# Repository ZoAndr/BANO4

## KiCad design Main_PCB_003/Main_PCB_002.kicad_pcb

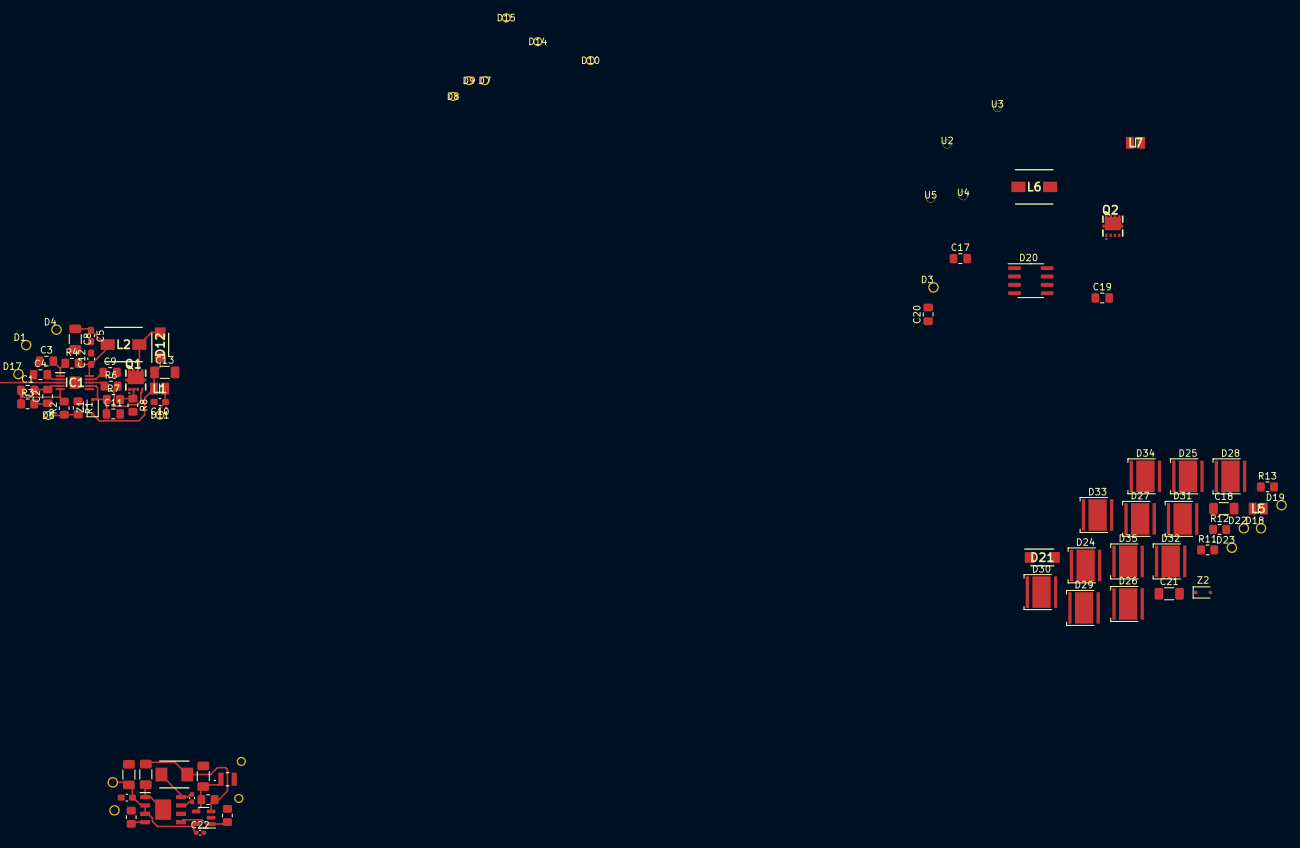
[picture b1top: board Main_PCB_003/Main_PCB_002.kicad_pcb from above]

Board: 4 copper layers, 88 parts (0 on the bottom side), 52 nets.

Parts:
C1, C2, C3, C4, C9, C11, C17, C19, C20: C; C_0805_2012Metric_Pad1.18x1.45mm_HandSolder
C5, C6, C10, C12: C; C_0603_1608Metric_Pad1.08x0.95mm_HandSolder
C7, C8, C13, C15, C16, C18, C21: C; C_1206_3216Metric_Pad1.33x1.80mm_HandSolder
C14, C22: C; C_0402_1005Metric_Pad0.74x0.62mm_HandSolder
D1, D2, D3, D4, D5, D17, D18, D19, D22, D23: WireHole_1p5; WireHole_1p2
D6, D7, D8, D9, D10, D11, D13, D14, D15, D16: Wire_Pad_01; Wire_Hole_1mm
D12, D21: SS36; SODFL4626X120N
D20: TX6211
D24, D25, D26, D27, D28, D29, D30, D31, D32, D33, D34, D35: LED_Cree_XHP50_6V; LED_Cree-XHP50_6V
IC1: TPS40211QDGQRQ1; SOP50P490X110-11N
IC2: LM5164QDDATQ1; SOIC127P600X170-9N
L1, L5, L7: TFM201610ALC-R47MTAA; INDC2016X80N
L2: SRP7050AA-220M; INDPM5752X300N
L3: SRP4020TA-100M; INDPM4441X200N
L4: TFM201610ALC-R47MTAA; WPN252010UR47MT
L6: TFM201610ALC-R47MTAA; INDPM5752X300N
Q1, Q2: AON7407; DFN_3X3_EP
R1, R2, R3, R4, R5, R6, R7, R8, R9, R10, R11, R12, R13: R; R_0805_2012Metric_Pad1.20x1.40mm_HandSolder
U1: INA138; SOT-23-5
U2, U3, U4, U5: Mounting_Hole_M2; Hole_screw_M1p2
Z1, Z2: BZT52-C5V1J; D_SOD-323F

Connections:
GND: C17.2, C18.2, C19.2, C20.2, C21.2, D3.1 (Conn), D19.1 (Conn), D20.1 (GND), R11.2, R13.2, U2.1 (Mnt), U3.1 (Mnt), U4.1 (Mnt), U5.1 (Mnt)
unnamed: C1.1, IC1.5 (FB), R2.2, R3.1
unnamed: C1.2, C2.2, IC1.4 (COMP)
unnamed: C2.1, R3.2
unnamed: C3.2, IC1.1 (RC), R4.1
unnamed: C4.2, IC1.2 (SS)
unnamed: C6.1, C7.1, C22.1, D5.1 (Conn), IC2.2 (VIN), IC2.3 (EN/UVLO), U1.5 (V+)
unnamed: C9.1, IC1.9 (BP)
unnamed: C10.1, D11.1 (Conn), L1.1
unnamed: C3.1, C4.1, C5.2, C8.2, C9.2, C10.2, C11.2, C12.2, C13.2, D1.1 (Conn), IC1.6 (GND), IC1.11 (EP), R1.1, R8.2
unnamed: C11.1, IC1.7 (ISNS), R7.1, Z1.2 (A)
unnamed: C5.1, C8.1, C12.1, D4.1 (Conn), IC1.10 (VDD), L2.1, R4.2
unnamed: C13.1, D12.1, L1.2, Z1.1 (K)
unnamed: C14.1, IC2.8 (SW), L3.1
unnamed: C14.2, IC2.7 (BST)
unnamed: C15.1, L3.2, R9.1, U1.3 (+)
unnamed: C6.2, C7.2, C15.2, C16.2, C22.2, D2.1 (Conn), D16.1 (Conn), IC2.1 (GND), IC2.9 (EP), R5.2, R10.1, U1.2 (GND)
unnamed: C16.1, L4.1, R9.2, U1.4 (-)
unnamed: C17.1, D20.3 (Comp)
unnamed: C18.1, C20.1, D20.2 (En), D20.8 (Vdd), L5.2, L6.1
unnamed: C19.1, D20.7 (TOFF)
unnamed: C21.1, D21.1, L7.1, Z2.1 (K)
unnamed: D6.1 (Conn), R1.2, R2.1
unnamed: D7.1 (Conn), D8.1 (Conn)
unnamed: D9.1 (Conn), D10.1 (Conn)
unnamed: D12.2, L2.2, Q1.5 (D_1), Q1.6 (D_2), Q1.7 (D_3), Q1.8 (D_4), Q1.9, Q1.10, Q1.11
unnamed: D13.1 (Conn), L4.2
unnamed: D14.1 (Conn), D15.1 (Conn)
unnamed: D17.1 (Conn), IC1.3 (DIS/~EN)
unnamed: D18.1 (Conn), L5.1
unnamed: D20.4 (VFB), R12.1, Z2.2 (A)
unnamed: D20.5 (DRV), Q2.4 (G)
unnamed: D20.6 (ICS), Q2.1 (S_1), Q2.2 (S_2), Q2.3 (S_3), R11.1
unnamed: D21.2, L6.2, Q2.5 (D_1), Q2.6 (D_2), Q2.7 (D_3), Q2.8 (D_4)
unnamed: D22.1 (Conn), D35.1 (K), R12.2, R13.1
unnamed: D23.1 (Conn), D24.2 (A), L7.2
unnamed: D24.1 (K), D25.2 (A)
unnamed: D25.1 (K), D26.2 (A)
unnamed: D26.1 (K), D27.2 (A)
unnamed: D27.1 (K), D28.2 (A)
unnamed: D28.1 (K), D29.2 (A)
unnamed: D29.1 (K), D30.2 (A)
unnamed: D30.1 (K), D31.2 (A)
unnamed: D31.1 (K), D32.2 (A)
unnamed: D32.1 (K), D33.2 (A)
unnamed: D33.1 (K), D34.2 (A)
unnamed: D34.1 (K), D35.2 (A)
unnamed: IC1.8 (GDRV), R6.1
unnamed: IC2.4 (RON), R5.1
unnamed: IC2.5 (FB), R10.2, U1.1
unnamed: Q1.1 (S_1), Q1.2 (S_2), Q1.3 (S_3), R7.2, R8.1
unnamed: Q1.4 (G), R6.2

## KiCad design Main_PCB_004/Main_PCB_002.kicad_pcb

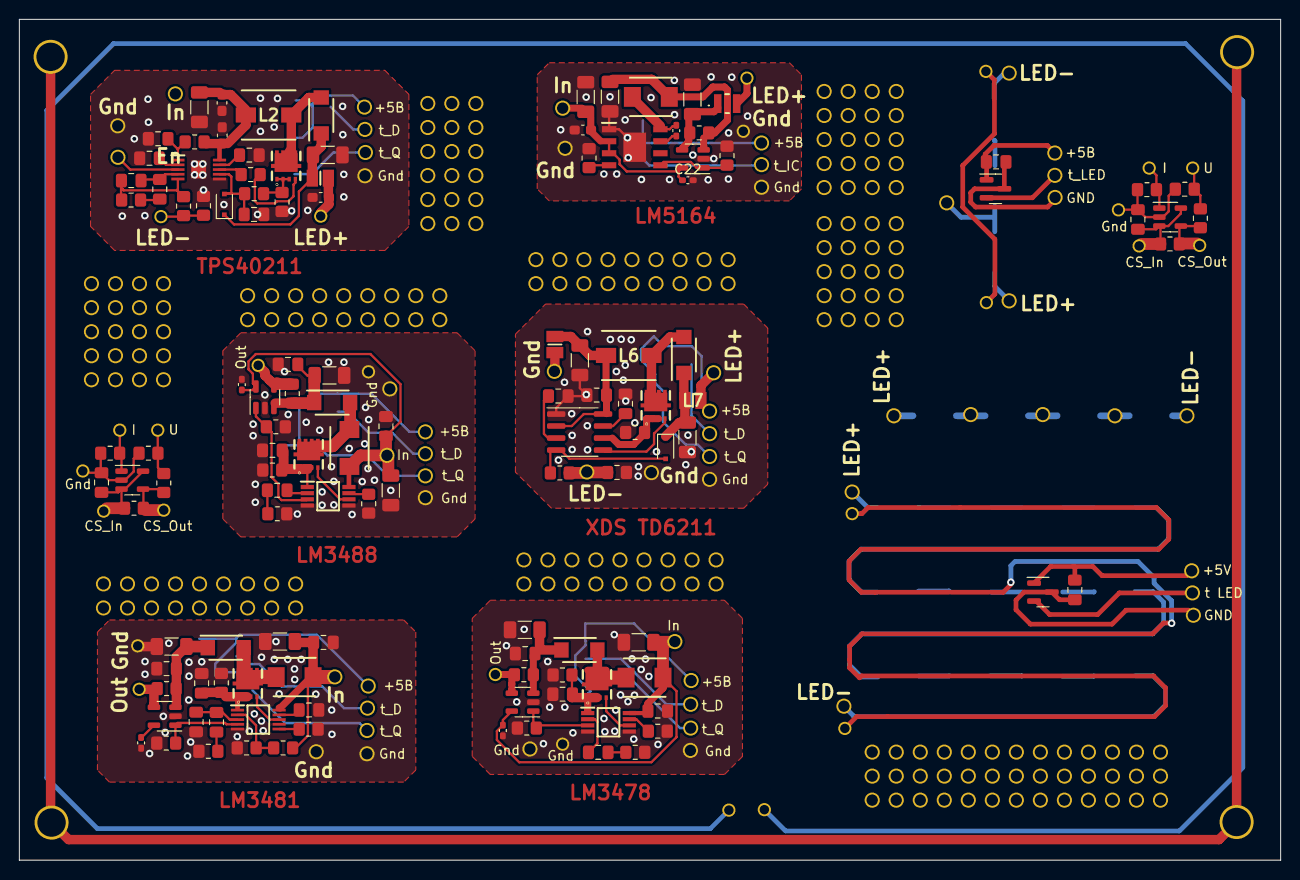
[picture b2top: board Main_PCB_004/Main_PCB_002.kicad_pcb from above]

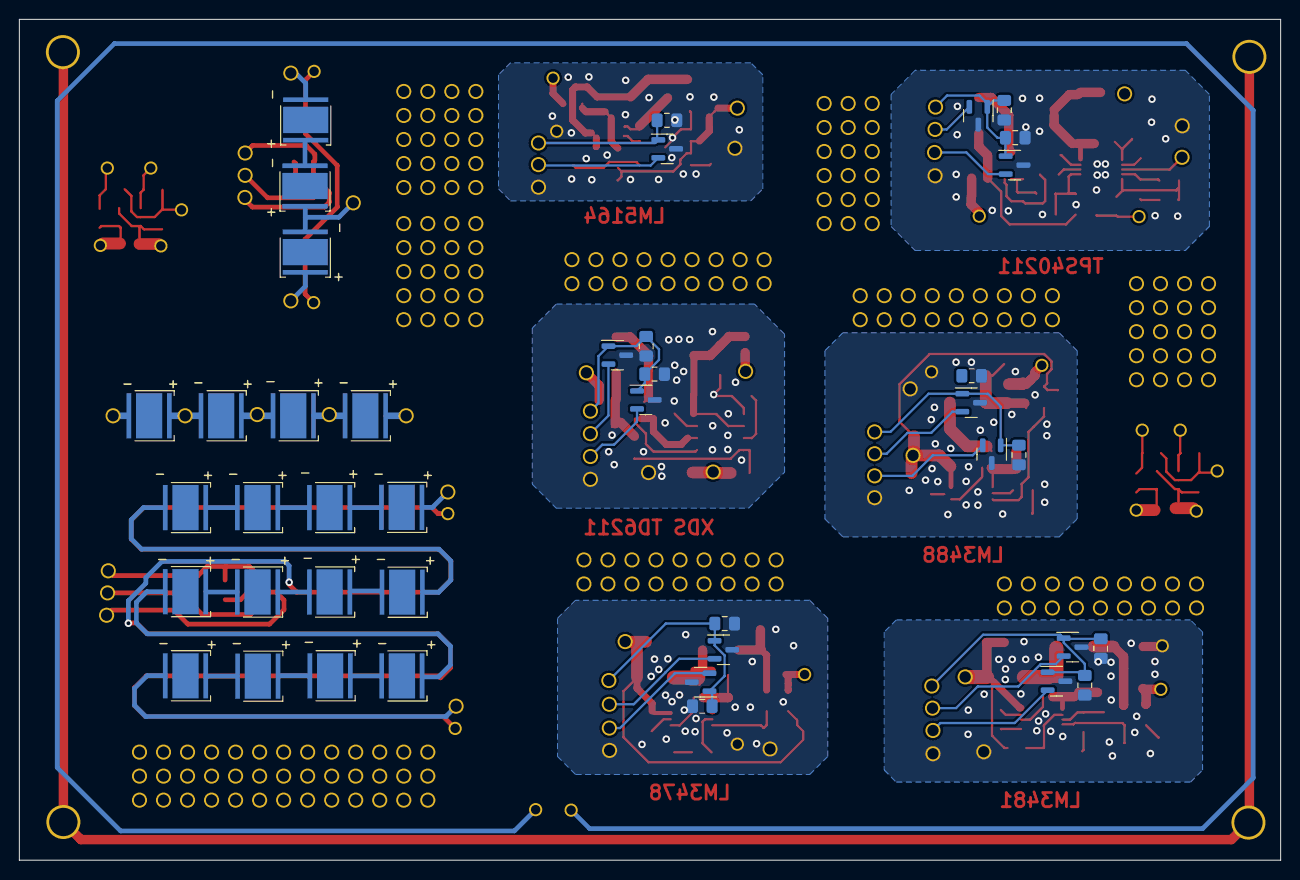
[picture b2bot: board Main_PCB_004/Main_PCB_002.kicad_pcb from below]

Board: 2 copper layers, 133.3 x 88.9 mm, 243 parts (41 on the bottom side), 128 nets.

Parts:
C1, C2, C3, C4, C9, C11, C17, C19, C20, C23, C24, C25, C27, C28, C30, C32, C33, C36, C37, C38, C39, C42, C43, C46, C47, C48, C49, C50, C51, C52, C53, C54, C55, C56, C57, C58, C59, C60: C; C_0805_2012Metric_Pad1.18x1.45mm_HandSolder
C5, C6, C10, C12: C; C_0603_1608Metric_Pad1.08x0.95mm_HandSolder
C7, C8, C13, C15, C16, C18, C21, C26, C29, C34, C35, C40, C41: C; C_1206_3216Metric_Pad1.33x1.80mm_HandSolder
C14, C22, C31, C44, C45: C; C_0402_1005Metric_Pad0.74x0.62mm_HandSolder
D1, D2, D3, D4, D5, D17, D18, D19, D22, D23, D36, D37, D43, D44, D55, D56, D57: WireHole_1p5; WireHole_1p2
D6, D7, D8, D9, D10, D11, D13, D14, D15, D16, D39, D53, D54: Wire_Pad_01; Wire_Hole_1mm
D12, D21, D38, D45, D46: SS36; SODFL4626X120N
D20: TX6211
D24, D25, D26, D27, D28, D29, D30, D31, D32, D33, D33#2, D33#3, D33#4, D33#5, D34, D35, D47, D48, D49: LED_Cree_XHP50_6V; LED_Cree-XHP50_6V
D40, D52, D72, D89: Gnd; Wire_Hole_1mm
D41, D61, D65, D69, D77, D83, D87: Gnd; WireHole_1p2
D42: In; WireHole_1p2
D50: Flash LED +; WireHole_1p2
D51: Out; Wire_Hole_1mm
D58: Flash LED -; WireHole_1p2
D59, D62, D66, D74, D80, D84, D95: +5B; WireHole_1p2
D60: t_IC; WireHole_1p2
D63, D67, D75, D81, D85: t_D; WireHole_1p2
D64, D68, D76, D82, D86: t_Q; WireHole_1p2
D70, D79: CS_In; Wire_Hole_1mm
D71, D88: CS_Out; Wire_Hole_1mm
D73, D90: U; Wire_Hole_1mm
D78, D91: I; Wire_Hole_1mm
D92: +5V; WireHole_1p2
D93: t LED; WireHole_1p2
D94, D97: GND; WireHole_1p2
D96: t_LED; WireHole_1p2
IC1: TPS40211QDGQRQ1; SOP50P490X110-11N
IC2: LM5164QDDATQ1; SOIC127P600X170-9N
IC3: LM3481MM_NOPB; SOP50P490X110-10N
IC4: LM3488MM; SOP65P490X110-8N
IC5: LM3478MMX_NOPB; SOP65P490X110-8N
L1, L5, L7: TFM201610ALC-R47MTAA; INDC2016X80N
L2: SRP7050AA-220M; INDPM5752X300N
L3, L8, L9, L10: SRP4020TA-100M; INDPM4441X200N
L4: TFM201610ALC-R47MTAA; WPN252010UR47MT
L6: TFM201610ALC-R47MTAA; INDPM5752X300N
Q1, Q2, Q3, Q4, Q5: AON7407; DFN_3X3_EP
R1, R2, R3, R4, R5, R6, R7, R8, R9, R10, R11, R12, R13, R14, R15, R16, R17, R18, R19, R20, R21, R22, R23, R24, R25, R26, R27, R28, R29, R30, R31, R32, R33, R34, R35, R36, R37, R38: R; R_0805_2012Metric_Pad1.20x1.40mm_HandSolder
U1, U6, U7, U8, U14, U21: INA138; SOT-23-5
U2, U4, U5: Mounting_Hole_M2; Hole_screw_M1p2
U9, U10, U11, U12, U13, U15, U16, U17, U18, U19, U20, U22, U23: MCP9700AT-ETT; SOT-23
Z1, Z2: BZT52-C5V1J; D_SOD-323F

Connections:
GND: D3.1 (Conn), U2.1 (Mnt), U4.1 (Mnt), U5.1 (Mnt)
unnamed: C1.1, IC1.5 (FB), R2.2, R3.1
unnamed: C1.2, C2.2, IC1.4 (COMP)
unnamed: C2.1, R3.2
unnamed: C3.2, IC1.1 (RC), R4.1
unnamed: C4.2, IC1.2 (SS)
unnamed: C9.1, IC1.9 (BP)
unnamed: C10.1, D11.1 (Conn), L1.1
unnamed: C3.1, C4.1, C5.2, C8.2, C9.2, C10.2, C11.2, C12.2, C13.2, C49.2, C50.2, D1.1 (Conn), D69.1 (Conn), IC1.6 (GND), IC1.11 (EP), R1.1, R8.2, U12.3 (GND), U13.3 (GND)
unnamed: C11.1, IC1.7 (ISNS), R7.1, Z1.2 (A)
unnamed: C5.1, C8.1, C12.1, D4.1 (Conn), IC1.10 (VDD), L2.1, R4.2
unnamed: C13.1, D12.1, L1.2, Z1.1 (K)
unnamed: C14.1, IC2.8 (SW), L3.1
unnamed: C14.2, IC2.7 (BST)
unnamed: C15.1, L3.2, R9.1, U1.3 (+)
unnamed: C6.2, C7.2, C15.2, C16.2, C22.2, C46.2, D2.1 (Conn), D16.1 (Conn), D61.1 (Conn), IC2.1 (GND), IC2.9 (EP), R5.2, R10.1, U1.2 (GND), U9.3 (GND)
unnamed: C16.1, L4.1, R9.2, U1.4 (-)
unnamed: C17.1, D20.3 (Comp)
unnamed: C18.1, C20.1, D20.2 (En), D20.8 (Vdd), L5.2, L6.1
unnamed: C19.1, D20.7 (TOFF)
unnamed: C21.1, D21.1, L7.1, Z2.1 (K)
unnamed: C6.1, C7.1, C22.1, D5.1 (Conn), IC2.2 (VIN), IC2.3 (EN/UVLO), U1.5 (V+)
unnamed: C23.1, C25.2, C26.2, C27.2, C28.2, C29.2, C30.2, C31.2, C47.2, C48.2, D37.1 (Conn), D40.1 (Conn), D65.1 (Conn), IC3.5 (AGND), IC3.7 (PGND), R14.1, R15.1, R17.2, R18.2, R20.1, U6.2 (GND), U10.3 (GND), U11.3 (GND)
unnamed: C23.2, C24.2, IC3.3 (COMP)
unnamed: C24.1, R14.2
unnamed: C25.1, IC3.9 (VCC)
unnamed: C26.1, C27.1, D36.1 (Conn), IC3.10 (VIN), L8.1, R16.2
unnamed: C28.1, IC3.1 (ISEN), Q3.1 (S_1), Q3.2 (S_2), Q3.3 (S_3), R18.1
unnamed: C29.1, C30.1, D38.1, R19.1, U6.3 (+)
unnamed: C31.1, U6.5 (V+)
unnamed: C32.1, R21.1
unnamed: C32.2, IC4.2 (COMP)
unnamed: C33.1, R22.1
unnamed: C33.2, IC5.2 (COMP)
unnamed: C34.1, C36.1, C44.1, D42.1 (Conn), IC5.8 (VIN), L9.1, U7.5 (V+)
unnamed: C34.2, C36.2, C38.2, C40.2, C42.2, C44.2, C54.2, C56.2, D41.1 (Conn), D52.1 (Conn), D83.1 (Conn), IC5.4 (AGND), IC5.5 (PGND), R22.2, R23.2, R25.2, R28.1, U7.2 (GND), U17.3 (GND), U19.3 (GND)
unnamed: C35.1, C37.1, C45.1, D43.1 (Conn), IC4.8 (VIN), L10.1, U8.5 (V+)
unnamed: C35.2, C37.2, C39.2, C41.2, C43.2, C45.2, C55.2, C57.2, D44.1 (Conn), D54.1 (Conn), D87.1 (Conn), IC4.4 (AGND), IC4.5 (PGND), R21.2, R24.2, R26.2, R30.1, U8.2 (GND), U18.3 (GND), U20.3 (GND)
unnamed: C38.1, IC5.1 (ISEN), Q4.1 (S_1), Q4.2 (S_2), Q4.3 (S_3), R25.1
unnamed: C39.1, IC4.1 (ISEN), Q5.1 (S_1), Q5.2 (S_2), Q5.3 (S_3), R26.1
unnamed: C40.1, C42.1, D45.1, R27.1, U7.3 (+)
unnamed: C41.1, C43.1, D46.1, R29.1, U8.3 (+)
unnamed: C46.1, D59.1 (Conn), U9.1 (Vdd)
unnamed: C47.1, C48.1, D62.1 (Conn), U10.1 (Vdd), U11.1 (Vdd)
unnamed: C49.1, C50.1, D66.1 (Conn), U12.1 (Vdd), U13.1 (Vdd)
unnamed: C51.1, D70.1 (Conn), R31.1, U14.3 (+), U14.5 (V+)
unnamed: C51.2, D72.1 (Conn), R32.1, R34.1, U14.2 (GND)
unnamed: C52.1, C53.1, D74.1 (Conn), U15.1 (Vdd), U16.1 (Vdd)
unnamed: C17.2, C18.2, C19.2, C20.2, C21.2, C52.2, C53.2, D19.1 (Conn), D20.1 (GND), D77.1 (Conn), R11.2, R13.2, U15.3 (GND), U16.3 (GND)
unnamed: C54.1, C56.1, D80.1 (Conn), U17.1 (Vdd), U19.1 (Vdd)
unnamed: C55.1, C57.1, D84.1 (Conn), U18.1 (Vdd), U20.1 (Vdd)
unnamed: C58.1, D79.1 (Conn), R35.1, U21.3 (+), U21.5 (V+)
unnamed: C58.2, D89.1 (Conn), R36.1, R38.1, U21.2 (GND)
unnamed: C59.1, D92.1 (Conn), U22.1 (Vdd)
unnamed: C59.2, D94.1 (Conn), U22.3 (GND)
unnamed: C60.1, D95.1 (Conn), U23.1 (Vdd)
unnamed: C60.2, D97.1 (Conn), U23.3 (GND)
unnamed: D6.1 (Conn), R1.2, R2.1
unnamed: D7.1 (Conn), D8.1 (Conn)
unnamed: D9.1 (Conn), D10.1 (Conn)
unnamed: D12.2, L2.2, Q1.5 (D_1), Q1.6 (D_2), Q1.7 (D_3), Q1.8 (D_4), Q1.9, Q1.10, Q1.11
unnamed: D13.1 (Conn), L4.2
unnamed: D14.1 (Conn), D15.1 (Conn)
unnamed: D17.1 (Conn), IC1.3 (DIS/~EN)
unnamed: D18.1 (Conn), L5.1
unnamed: D20.4 (VFB), R12.1, Z2.2 (A)
unnamed: D20.5 (DRV), Q2.4 (G)
unnamed: D20.6 (ICS), Q2.1 (S_1), Q2.2 (S_2), Q2.3 (S_3), R11.1
unnamed: D21.2, L6.2, Q2.5 (D_1), Q2.6 (D_2), Q2.7 (D_3), Q2.8 (D_4), Q2.9, Q2.10, Q2.11
unnamed: D22.1 (Conn), R12.2, R13.1
unnamed: D23.1 (Conn), L7.2
unnamed: D24.1 (K), D25.2 (A)
unnamed: D24.2 (A), D50.1 (Conn)
unnamed: D25.1 (K), D26.2 (A)
unnamed: D26.1 (K), D27.2 (A)
unnamed: D27.1 (K), D28.2 (A)
unnamed: D28.1 (K), D29.2 (A)
unnamed: D29.1 (K), D30.2 (A)
unnamed: D30.1 (K), D31.2 (A)
unnamed: D31.1 (K), D32.2 (A)
unnamed: D32.1 (K), D33#3.2 (A)
unnamed: D33#3.1 (K), D34.2 (A)
unnamed: D34.1 (K), D35.2 (A)
unnamed: D35.1 (K), D58.1 (Conn)
unnamed: D38.2, L8.2, Q3.5 (D_1), Q3.6 (D_2), Q3.7 (D_3), Q3.8 (D_4), Q3.9, Q3.10, Q3.11
unnamed: D39.1 (Conn), R19.2, U6.4 (-)
unnamed: D45.2, L9.2, Q4.5 (D_1), Q4.6 (D_2), Q4.7 (D_3), Q4.8 (D_4), Q4.9, Q4.10, Q4.11
unnamed: D46.2, L10.2, Q5.5 (D_1), Q5.6 (D_2), Q5.7 (D_3), Q5.8 (D_4), Q5.9, Q5.10, Q5.11
unnamed: D47.1 (K), D48.2 (A)
unnamed: D47.2 (A), D55.1 (Conn)
unnamed: D48.1 (K), D49.2 (A), D56.1 (Conn)
unnamed: D49.1 (K), D57.1 (Conn)
unnamed: D51.1 (Conn), R27.2, U7.4 (-)
unnamed: D53.1 (Conn), R29.2, U8.4 (-)
unnamed: D60.1 (Conn), U9.2 (Vout)
unnamed: D63.1 (Conn), U11.2 (Vout)
unnamed: D64.1 (Conn), U10.2 (Vout)
unnamed: D67.1 (Conn), U13.2 (Vout)
unnamed: D68.1 (Conn), U12.2 (Vout)
unnamed: D71.1 (Conn), R31.2, R33.2, U14.4 (-)
unnamed: D73.1 (Conn), R33.1, R34.2
unnamed: D75.1 (Conn), U16.2 (Vout)
unnamed: D76.1 (Conn), U15.2 (Vout)
unnamed: D78.1 (Conn), R32.2, U14.1
unnamed: D81.1 (Conn), U19.2 (Vout)
unnamed: D82.1 (Conn), U17.2 (Vout)
unnamed: D85.1 (Conn), U20.2 (Vout)
unnamed: D86.1 (Conn), U18.2 (Vout)
unnamed: D88.1 (Conn), R35.2, R37.2, U21.4 (-)
unnamed: D90.1 (Conn), R37.1, R38.2
unnamed: D91.1 (Conn), R36.2, U21.1
unnamed: D93.1 (Conn), U22.2 (Vout)
unnamed: D96.1 (Conn), U23.2 (Vout)
unnamed: IC1.8 (GDRV), R6.1
unnamed: IC2.4 (RON), R5.1
unnamed: IC2.5 (FB), R10.2, U1.1
unnamed: IC3.2 (UVLO), R15.2, R16.1
unnamed: IC3.4 (FB), R20.2, U6.1
unnamed: IC3.6 (FA/SYNC/SD), R17.1
unnamed: IC3.8 (DR), Q3.4 (G)
unnamed: IC4.3 (FB), R30.2, U8.1
unnamed: IC4.6 (DR), Q5.4 (G)
unnamed: IC4.7 (FA/SYNC/SD), R24.1
unnamed: IC5.3 (FB), R28.2, U7.1
unnamed: IC5.6 (DR), Q4.4 (G)
unnamed: IC5.7 (FA/SD), R23.1
unnamed: Q1.1 (S_1), Q1.2 (S_2), Q1.3 (S_3), R7.2, R8.1
unnamed: Q1.4 (G), R6.2

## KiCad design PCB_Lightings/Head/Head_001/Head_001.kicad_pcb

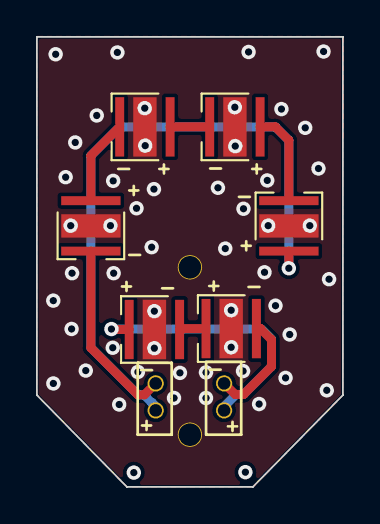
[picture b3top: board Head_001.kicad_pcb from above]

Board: 2 copper layers, 17.0 x 25.0 mm, 12 parts (0 on the bottom side), 9 nets.

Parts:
D1, D2, D3, D4, D5, D8: LED_Cree_XHP50_6V; LED_Cree-XHP35
D6, D7, D9, D10: Conn_Hole_0p7; WireHole_0p7
U1, U2: Mounting_Hole_M2; Hole_screw_M1p2

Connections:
unnamed: D1.1 (K), D10.1
unnamed: D1.2 (A), D3.1 (K)
unnamed: D1.3 (PAD), D2.3 (PAD), D3.3 (PAD), D4.3 (PAD), D5.3 (PAD), D8.3 (PAD), U1.1 (Mnt), U2.1 (Mnt)
unnamed: D2.1 (K), D7.1
unnamed: D2.2 (A), D4.1 (K)
unnamed: D3.2 (A), D5.1 (K)
unnamed: D4.2 (A), D6.1
unnamed: D5.2 (A), D8.1 (K)
unnamed: D8.2 (A), D9.1
